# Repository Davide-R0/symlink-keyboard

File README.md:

# Keyboard

## Tools

- Build123d: for the viewer look [external editors](https://build123d.readthedocs.io/en/latest/external.html#external), in general we use: `yet-another-cad-viewer` (c'è una estensione per nvim o vscode?)
- SKiDL: to convert form kicad use tool: `netlist_to_skidl` (TODO: setup kicad liberary for this)
- Openscad to build123 migration: [look here](https://build123d.readthedocs.io/en/latest/OpenSCAD.html)
- for the pcb routing still use kicad editor

## General proprieties

- Layout `4x6+5`
- Parte sinistra il master, destro slave
- Si pososno caricare due firmwere diversi:
  - Bluetooth tra le due parti, se collegato il cavo intermedio e collegato il master al pc si caricano entrambe le schede. In entrambi i casi si può o collegare col cavo al pc per avere cablato il master o col bluetooth col master.
  - Cablato tra le due parti, in questo caso bisogna collegare il cavo tra le due parti e poi si può decidere se collegarla al pc tramite bluetooth o cavo con il master.
- led rgb per key e anche sul retro (led sotto tasti e sul retro sono in due lineee dati separati perchè quando va con batteria funzionano solo quelli sul retro, quando colelgato via cavo funzionano entrambi)
- schermo oled e potenziometro per lato
- Case "Sandwich Mount"
- Framework: `ZMK`, si possono creare moduli in C, supporta BLE e il nice!nano v2.
- Round trackpad (Circle Touchpad), mini touchpad. Il `TM023023-2024` su `Mouser` (c'è sia con overlay che senza, si può usare un nastro personalizzato se si vuole: ) per il connettore: connettore FPC 12-pin, 0.5mm pitch, bottom contact (52746-1271 ?). Altrimenti già completo (ma grande): [splitkb](https://splitkb.com/products/halcyon-cirque-touchpad-module?_pos=1&_sid=2299becd1&_ss=r). NOTA: forse ci sta anche al verisone da 35mm di diametro)

## Components

- Un micorcontroller `nice!nano v2` per lato (Pro Micro NRF52840) (Amazon o Aliexpress)
- Una batteria per lato sotto il microcontroller: `303040`, per la batteria forse fare un dopio fondo (cioè tagliare la back pcb e metterne un'altra che sporge di più sul retro così da poter mettere batterie più spesse (503040 o 503050)) (Aliexpress)
NOTE: le batterie anderebbero sempre circa 400-500mA (`403040`) a destra e 700-800mA (`403050`) a sinistra per consumo giusto.
- Un pannello oled per lato `0.91 inch OLED LCD Display IIC 128×32` (Amazon o Aliexpress)
- Un potenziometro a sinistra: `EC11` con click (LCSC)
- Un Circle Touchpad a destra: [splitkb](https://splitkb.com/products/halcyon-cirque-touchpad-module?_pos=1&_sid=2299becd1&_ss=r). Per la connesisone c'è bisogno di:
  - FPC a 12 pin: `FPC-05F-6PH20` (LCSC) (NOTE: è difficile da saldare? se dovesse essere cercare i "FPC to DIP breakout 12 pin 0.5mm")
  - Per il trackpad c'è un problema: macano i pin, bisogna usare un io expander: `PCA9536D` (4 pin extra) (LCSC)
- I switch `Kailh Choc V2 'Deep Sea' Brown` (tattili, low profile, silenziosi, con alloggio a croce) (Aliexpress)
- Socket per i switch `Kailh Choc Low Profile Socket` compatibili con choc. (Aliexpress) TODO: rivedere socket compatibili!
- Led rgb `SK6812MINI-E` per switch (trought hole) (LCSC)
- Led RGB `SK6812-5050` per la retorilluminazione (x6 per lato) (LCSC)a
- Per i led rgb di va un circuito che scollega l'alimentazione se non servonoe:
  - -- Transistor P-CH mosfet: `AO3401A` SOT-23 (LCSC)
  - -- Transistor N-CH mosfet: `AO3400A` SOT-23 (LCSC)
  - -- Resistena 100kohm: `ERJ6ENF1003V` 0805, per il pull-down per il P-CH (LCSC)
  - -- Resistena 10kohm: `TE05H1002BT` 0805, per il pull-up per il N-CH (LCSC)
  - Al posto dei mosfet grandi e resistenze meglio come: `TPS22917` + condensatore da 1nF: `CL21C102JBCNNNC` (LCSC)
- Resistenze 4.7kohm: `ERJU6RD4701V` 0805, per pullup per SDA e SCL (LCSC)
- Resistenza 400ohm: `TR0805B400RP0525Z` 0805, per l'ingresso DIN dei led (potrebbero esserci sovralimentazioni) (LCSC)
- Diodi: `1N4148W-E3-08` in SOD-123 per i led (cambiare il formato per facilità di saldatura?) (LCSC)
- Connection between split:
  - usb-c ports x2: `TYPE-C 16PIN 2MD`, per connessione tra due parti (LCSC)
  - ESD protection (Chip TVS): `USBLC6-2SC6`
  - PTC fuse (6V 1.5-2A): `1206L150/6V` (NOTE: forse meglio da 2A `1206L200/6V`) (LCSC)
  - Filtro RC per lo shield del usb-c: resistenza: (1kOhm) `RC0805FR-071KL`, condensatore (100nF 100V X7R) `CC0805X7R100V104MN`
  - Resistenza (5.1kohm): `0805W8F5101T5E`, per le connessioni pull-down CC1 CC2 (per alimentaizone)
  - Resistenza (22kohm) con supporto da 1.5A: `ERJ6ENF2202V`, per le connessioni pull-up CC1 CC2 (per alimentaizone)
  - Ideal Diode IC: `MAX40200AUK+T`, per il ritorno di corrente dalla porta (LCSC)
  - --Load switch IO (per protezione da correnti inverse): `TPS22918`
  - -- Diodi Zener da 3.3V: `BZT52C3V3-E3-18`, per protezione da collegamento scorretto (SOD-123) (LCSC)
  - -- resistenze: `0805W8F1000T5E`, 100 ohm 0805 per protezione da collegamento scorretto (LCSC)
- headers low profile: `Mill-Max Mfg. Corp. 315-43-112-41-003000`, to connect the nice!nano to the main pcb (and also the oled display) (LCSC) (OLD: header female connectors: `PM2.54-1X8PM-H85` (o altre versioni...))
- brass spacers M2 (+ viti): `Kit distanziatore in ottone` (Aliexpress)
- slider switch SMD : `PCM12SMTR`, per accendere/spegnere la batteria per ogni lato (LCSC)
- button SMD: verticale: `TL3342F450QG` oppure laterale: `SKSCLDE010`, per mettere la scheda in modalità bootloader. (LCSC)
- PCBs: "Sandwich Mount":
  - Layout:
    - Top Plate: dove voengono incastrati i switch
    - Main PCB: dove c'è tuta la elettornica
    - Bottom Plate: per proteggere la eletronica deall'esterno.
  - Il tutto connesso isnieme con viti M.2 e distanziali in ottone:
    - Tra il main pcb e il Top plate non is mettono distanziali perchè sono gli switch a tenere il palte.
    - Tra main pcb e botton plate: distanziali tra `6-8mm`.
  - Per la pendenza o si mettono distanziali assimmetrici,oppure si usa il `Tenting Puck`, (JLCPCB)
- Livellatore di tensione (Level Shifter): `SN74LVC1T45DBVR` per la linea dati dei led (LCSC)
- Per prioteggere sovratensioni TX/RX un Logic Buffer: `SN74LVC2G34DBVR` (LCSC)
- --Diodo Schottky: `SS14`, per il ritorno della batteria quando sono collegati tramite filo le due parti (LCSC)
- Kampton tape: per l'isolamento e resistenza al calore (Aliexpress)
- Pasta saldante: per componenti smd (Aliexpress)

Switch Kailh Choc V2: Ottimi, ma ricorda che hanno un'altezza diversa dai V1. Il tuo "Top Plate" deve avere uno spessore di $1.2\text{ mm}$ o $1.5\text{ mm}$ (taglio laser o PCB) per permettere agli switch di "cliccare" correttamente in posizione.

NOTE: per i componenti smd i formati da scegliere sono:

- SOT-23 per i chip a più gambe
- 0805 per R, C e componenti a 2 gambe

QT_QPA_PLATFORM=xcb freecad

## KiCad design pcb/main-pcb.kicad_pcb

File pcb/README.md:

skidl in python

 NOTE: per nvim è meglio lsp: basedpyright perchè più robusto

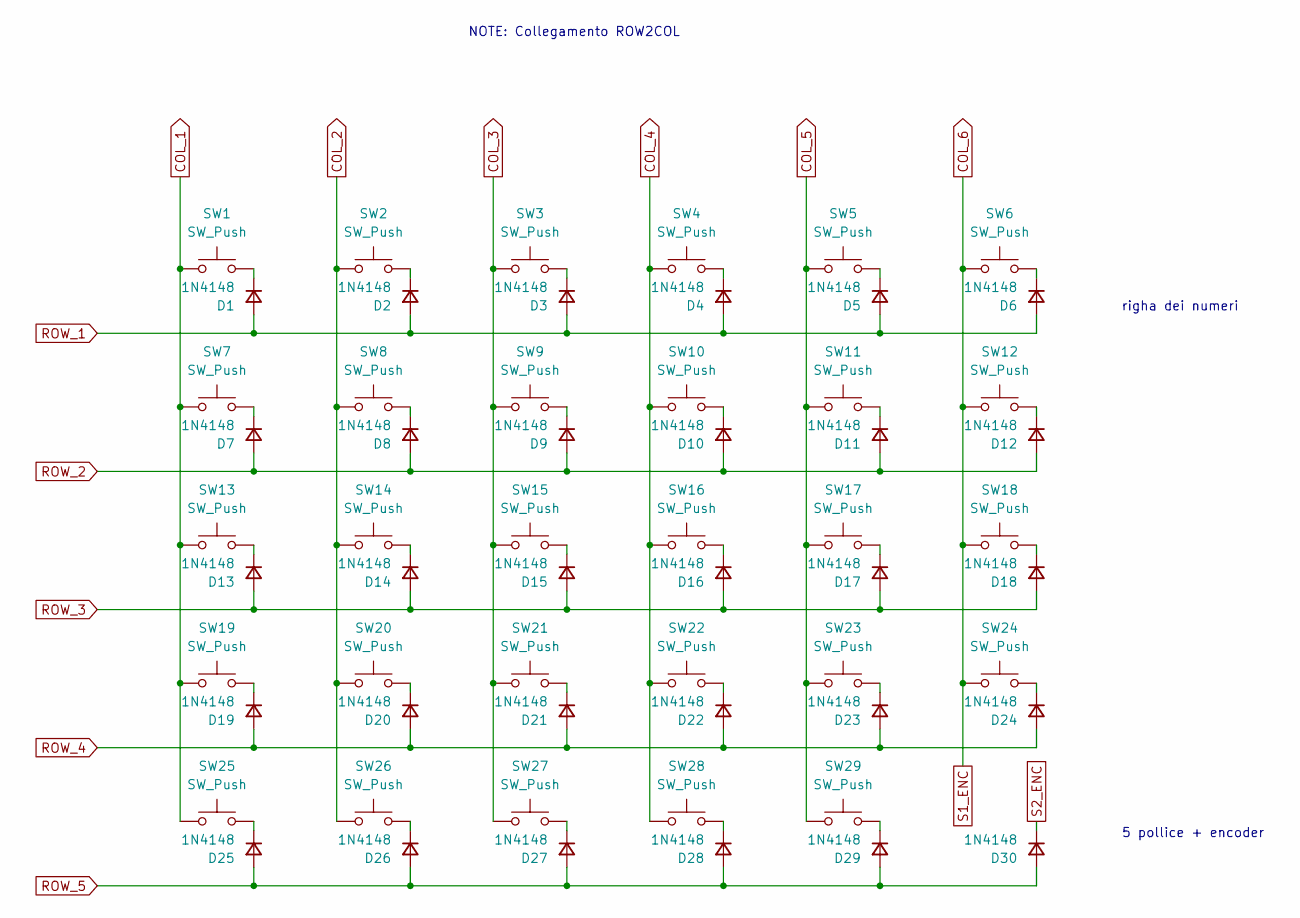
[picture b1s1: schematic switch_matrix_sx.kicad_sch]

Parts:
D1, D2, D3, D4, D5, D6, D7, D8, D9, D10, D11, D12, D13, D14, D15, D16, D17, D18, D19, D20, D21, D22, D23, D24, D25, D26, D27, D28, D29, D30: 1N4148; D_SOD-123
SW1, SW2, SW3, SW4, SW5, SW6, SW7, SW8, SW9, SW10, SW11, SW12, SW13, SW14, SW15, SW16, SW17, SW18, SW19, SW20, SW21, SW22, SW23, SW24, SW25, SW26, SW27, SW28, SW29: SW_Push; SW_Hotswap_Kailh_Choc_V2_1.00u

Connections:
COL_1: SW1.1, SW7.1, SW13.1, SW19.1, SW25.1; also elsewhere on the board
COL_2: SW2.1, SW8.1, SW14.1, SW20.1, SW26.1; also elsewhere on the board
COL_3: SW3.1, SW9.1, SW15.1, SW21.1, SW27.1; also elsewhere on the board
COL_4: SW4.1, SW10.1, SW16.1, SW22.1, SW28.1; also elsewhere on the board
COL_5: SW5.1, SW11.1, SW17.1, SW23.1, SW29.1; also elsewhere on the board
COL_6: SW6.1, SW12.1, SW18.1, SW24.1; also elsewhere on the board
unnamed: D1.1 (K), SW1.2
unnamed: D2.1 (K), SW2.2
unnamed: D3.1 (K), SW3.2
unnamed: D4.1 (K), SW4.2
unnamed: D5.1 (K), SW5.2
unnamed: D6.1 (K), SW6.2
unnamed: D7.1 (K), SW7.2
unnamed: D8.1 (K), SW8.2
unnamed: D9.1 (K), SW9.2
unnamed: D10.1 (K), SW10.2
unnamed: D11.1 (K), SW11.2
unnamed: D12.1 (K), SW12.2
unnamed: D13.1 (K), SW13.2
unnamed: D14.1 (K), SW14.2
unnamed: D15.1 (K), SW15.2
unnamed: D16.1 (K), SW16.2
unnamed: D17.1 (K), SW17.2
unnamed: D18.1 (K), SW18.2
unnamed: D19.1 (K), SW19.2
unnamed: D20.1 (K), SW20.2
unnamed: D21.1 (K), SW21.2
unnamed: D22.1 (K), SW22.2
unnamed: D23.1 (K), SW23.2
unnamed: D24.1 (K), SW24.2
unnamed: D25.1 (K), SW25.2
unnamed: D26.1 (K), SW26.2
unnamed: D27.1 (K), SW27.2
unnamed: D28.1 (K), SW28.2
unnamed: D29.1 (K), SW29.2
ROW_1: D1.2 (A), D2.2 (A), D3.2 (A), D4.2 (A), D5.2 (A), D6.2 (A); also elsewhere on the board
ROW_2: D7.2 (A), D8.2 (A), D9.2 (A), D10.2 (A), D11.2 (A), D12.2 (A); also elsewhere on the board
ROW_3: D13.2 (A), D14.2 (A), D15.2 (A), D16.2 (A), D17.2 (A), D18.2 (A); also elsewhere on the board
ROW_4: D19.2 (A), D20.2 (A), D21.2 (A), D22.2 (A), D23.2 (A), D24.2 (A); also elsewhere on the board
ROW_5: D25.2 (A), D26.2 (A), D27.2 (A), D28.2 (A), D29.2 (A), D30.2 (A); also elsewhere on the board
S2_ENC: D30.1 (K); also elsewhere on the board

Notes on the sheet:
NOTE: Collegamento ROW2COL
5 pollice + encoder
righa dei numeri

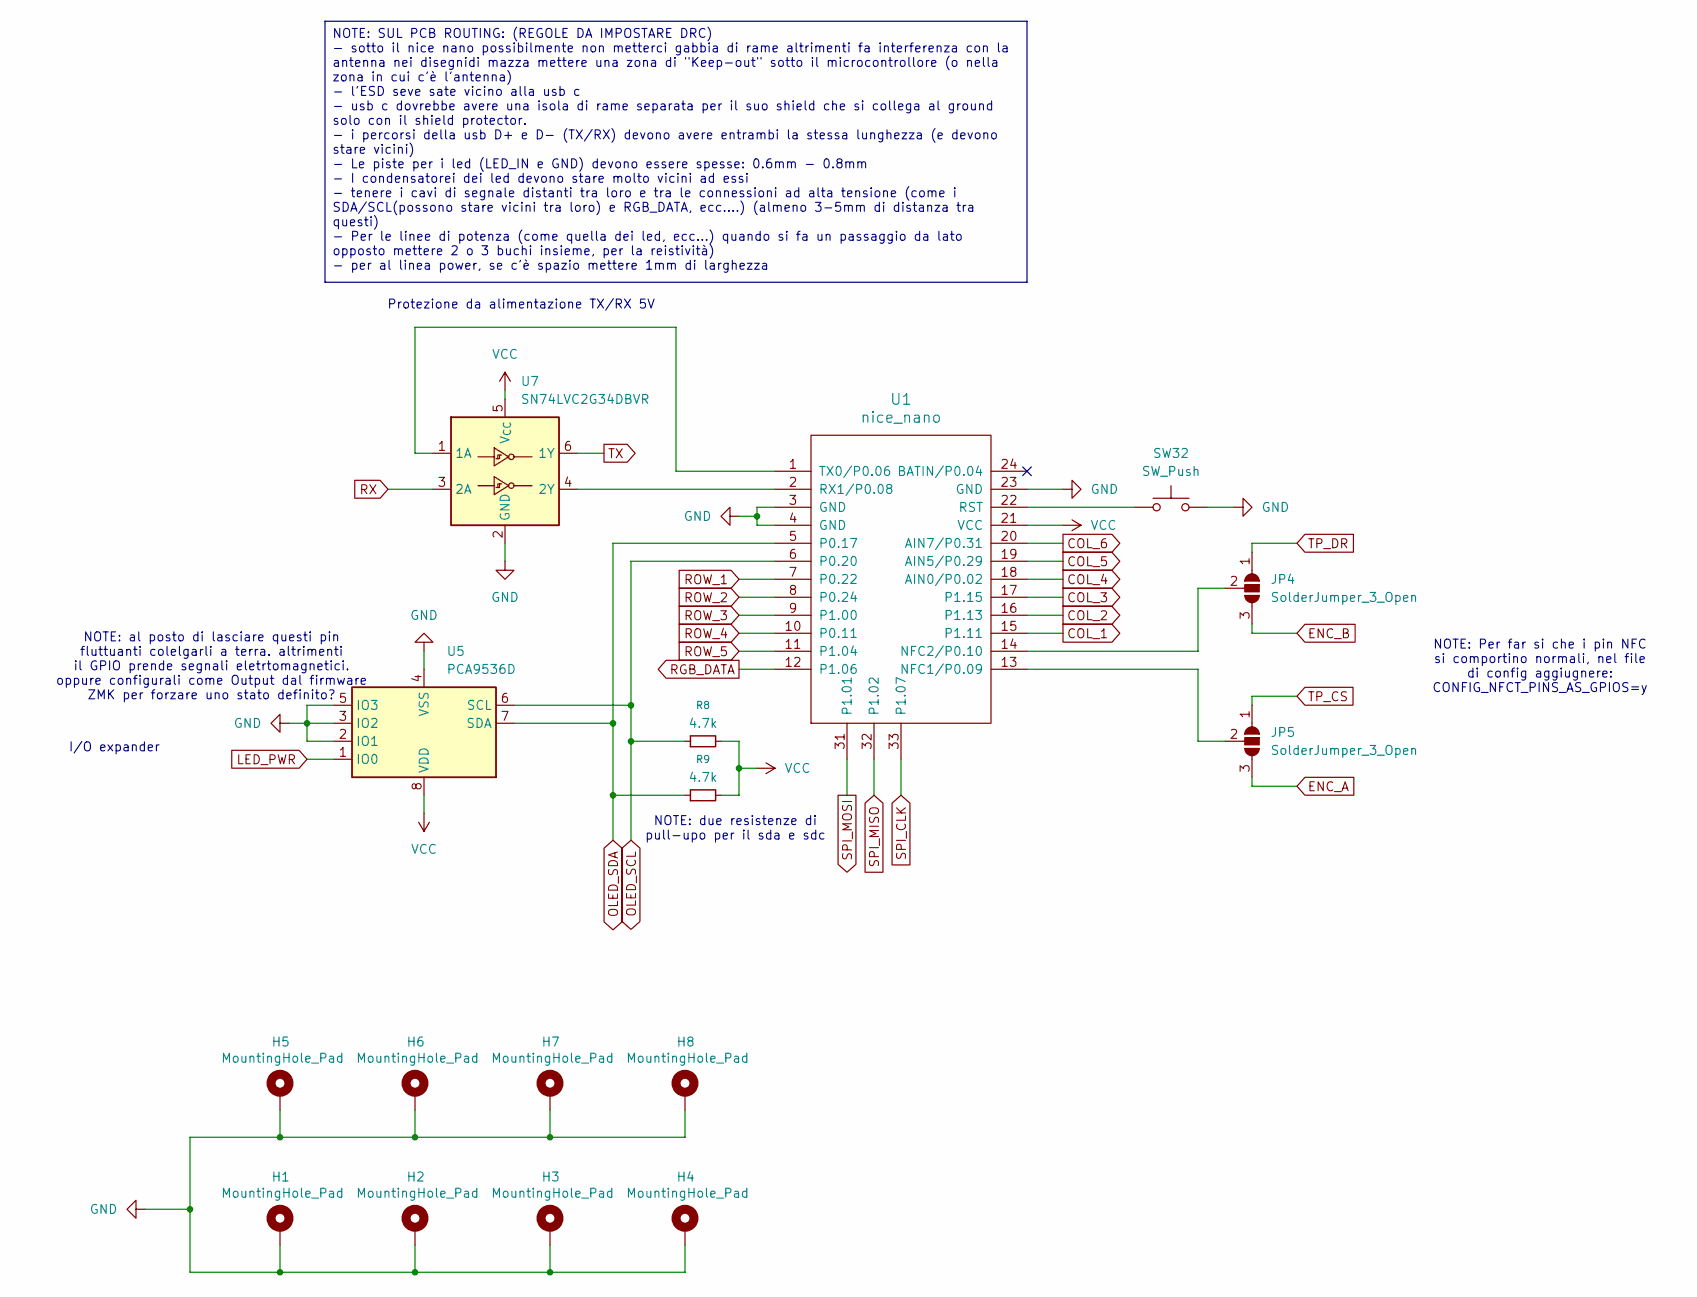
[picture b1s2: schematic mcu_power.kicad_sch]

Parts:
H1, H2, H3, H4, H5, H6, H7, H8: MountingHole_Pad
JP4, JP5: SolderJumper_3_Open; SolderJumper-3_P1.3mm_Open_RoundedPad1.0x1.5mm_NumberLabels
R8, R9: 4.7k; R_0805_2012Metric_Pad1.20x1.40mm_HandSolder
SW32: SW_Push; SW_SPST_TL3342
U1: nice_nano
U5: PCA9536D; SOIC-8_3.9x4.9mm_P1.27mm
U7: SN74LVC2G34DBVR; SOT-23-6

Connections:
COL_1: U1.15 (P1.11); also elsewhere on the board
COL_2: U1.16 (P1.13); also elsewhere on the board
COL_3: U1.17 (P1.15); also elsewhere on the board
COL_4: U1.18 (AIN0/P0.02); also elsewhere on the board
COL_5: U1.19 (AIN5/P0.29); also elsewhere on the board
COL_6: U1.20 (AIN7/P0.31); also elsewhere on the board
ENC_A: JP5.3 (B); also elsewhere on the board
ENC_B: JP4.3 (B); also elsewhere on the board
GND: H1.1, H2.1, H3.1, H4.1, H5.1, H6.1, H7.1, H8.1, SW32.2, U1.3 (GND), U1.4 (GND), U1.23 (GND), U5.2 (IO1), U5.3 (IO2), U5.4 (VSS), U5.5 (IO3), U7.2 (GND); also elsewhere on the board
LED_PWR: U5.1 (IO0); also elsewhere on the board
unnamed: JP4.2 (C), U1.14 (NFC2/P0.10)
unnamed: JP5.2 (C), U1.13 (NFC1/P0.09)
unnamed: SW32.1, U1.22 (RST)
unnamed: U1.2 (RX1/P0.08), U7.4 (2Y)
unnamed: U1.1 (TX0/P0.06), U7.1 (1A)
OLED_SCL: R8.1, U1.6 (P0.20), U5.6 (SCL); also elsewhere on the board
OLED_SDA: R9.1, U1.5 (P0.17), U5.7 (SDA); also elsewhere on the board
RGB_DATA: U1.12 (P1.06); also elsewhere on the board
ROW_1: U1.7 (P0.22); also elsewhere on the board
ROW_2: U1.8 (P0.24); also elsewhere on the board
ROW_3: U1.9 (P1.00); also elsewhere on the board
ROW_4: U1.10 (P0.11); also elsewhere on the board
ROW_5: U1.11 (P1.04); also elsewhere on the board
RX: U7.3 (2A); also elsewhere on the board
SPI_CLK: U1.33 (P1.07); also elsewhere on the board
SPI_MISO: U1.32 (P1.02); also elsewhere on the board
SPI_MOSI: U1.31 (P1.01); also elsewhere on the board
TP_CS: JP5.1 (A); also elsewhere on the board
TP_DR: JP4.1 (A); also elsewhere on the board
TX: U7.6 (1Y); also elsewhere on the board
VCC: R8.2, R9.2, U1.21 (VCC), U5.8 (VDD), U7.5 (V_{CC}); also elsewhere on the board

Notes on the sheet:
NOTE: Per far si che i pin NFC si comportino normali, nel file di config aggiugnere: CONFIG_NFCT_PINS_AS_GPIOS=y
NOTE: al posto di lasciare questi pin fluttuanti colelgarli a terra. altrimenti il GPIO prende segnali eletrtomagnetici. oppure configurali come Output dal firmware ZMK per forzare uno stato definito?
I/O expander
Protezione da alimentazione TX/RX 5V
NOTE: due resistenze di pull-upo per il sda e sdc
NOTE: SUL PCB ROUTING: (REGOLE DA IMPOSTARE DRC) - sotto il nice nano possibilmente non metterci gabbia di rame altrimenti fa interferenza con la antenna nei disegnidi mazza mettere una zona di "Keep-out" sotto il microcontrollore (o nella zona in cui c'è l'antenna) - l'ESD seve sate vicino alla us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

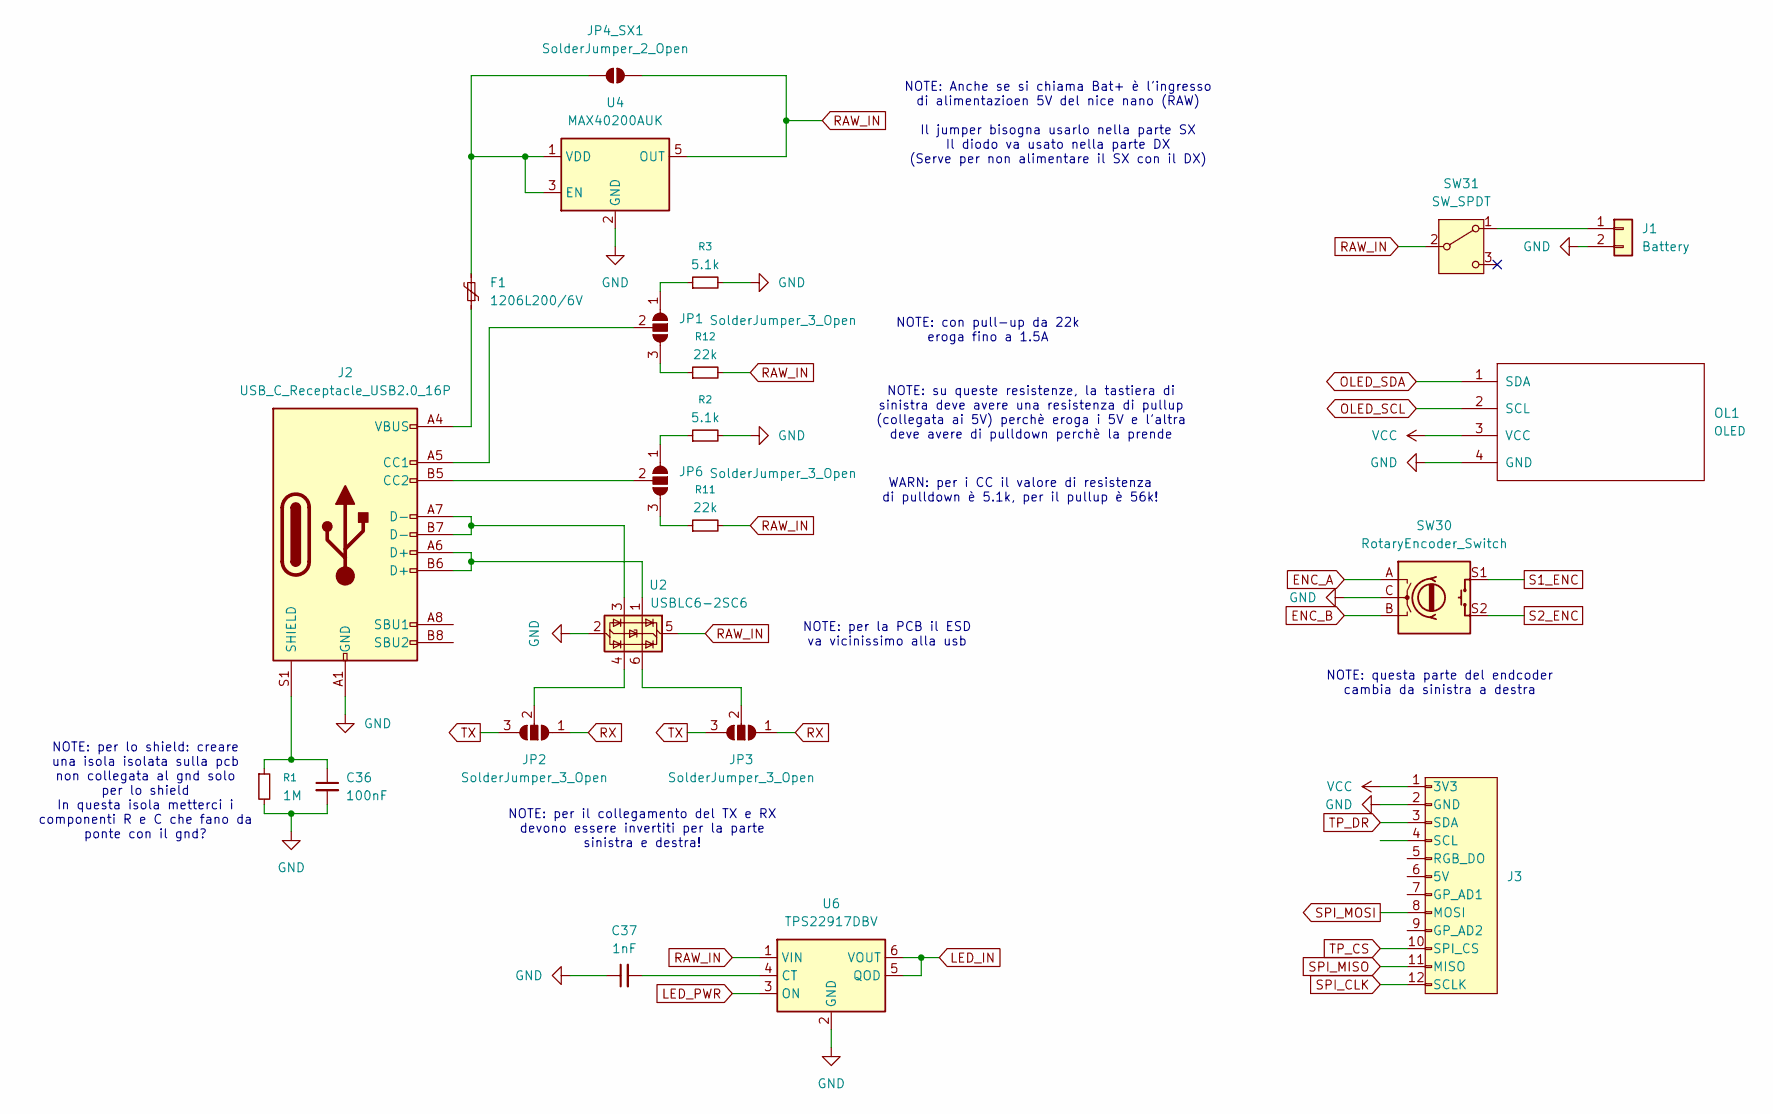
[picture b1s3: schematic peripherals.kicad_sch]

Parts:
C36: 100nF; C_0805_2012Metric_Pad1.18x1.45mm_HandSolder
C37: 1nF; C_0805_2012Metric_Pad1.18x1.45mm_HandSolder
F1: 1206L200/6V; Fuse_1206_3216Metric
J1: Battery; JST_PH_S2B-PH-K_1x02_P2.00mm_Horizontal
J2: USB_C_Receptacle_USB2.0_16P; USB_C_Receptacle_HRO_TYPE-C-31-M-12
J3: JUSHUO_AFA07-S12FCA-00_1x12-1MP_P1.0mm_Horizontal
JP1, JP2, JP3, JP6: SolderJumper_3_Open; SolderJumper-3_P1.3mm_Open_RoundedPad1.0x1.5mm_NumberLabels
JP4_SX1: SolderJumper_2_Open; SolderJumper-2_P1.3mm_Open_RoundedPad1.0x1.5mm
OL1: OLED; OLED_v2
R1: 1M; R_0805_2012Metric_Pad1.20x1.40mm_HandSolder
R2, R3: 5.1k; R_0805_2012Metric_Pad1.20x1.40mm_HandSolder
R11, R12: 22k; R_0805_2012Metric_Pad1.20x1.40mm_HandSolder
SW30: RotaryEncoder_Switch; RotaryEncoder_Alps_EC11E-Switch_Vertical_H20mm
SW31: SW_SPDT; SW_SPDT_PCM12
U2: USBLC6-2SC6; SOT-23-6
U4: MAX40200AUK; SOT-23-5
U6: TPS22917DBV; SOT-23-6

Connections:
COL_6: SW30.S1; also elsewhere on the board
ENC_A: SW30.A; also elsewhere on the board
ENC_B: SW30.B; also elsewhere on the board
GND: C36.2, C37.1, J1.2, J2.A1 (GND), J2.A12 (GND), J2.B1 (GND), J2.B12 (GND), J3.2 (GND), OL1.4 (GND), R1.2, R2.2, R3.2, SW30.C, U2.2 (GND), U4.2 (GND), U6.2 (GND); also elsewhere on the board
LED_IN: U6.5 (QOD), U6.6 (VOUT); also elsewhere on the board
LED_PWR: U6.3 (ON); also elsewhere on the board
unnamed: F1.1, J2.A4 (VBUS), J2.A9 (VBUS), J2.B4 (VBUS), J2.B9 (VBUS)
unnamed: J1.1, SW31.1 (A)
unnamed: J2.A5 (CC1), JP1.2 (C)
unnamed: J2.B5 (CC2), JP6.2 (C)
unnamed: J2.A6 (D+), J2.B6 (D+), U2.1 (I/O1)
unnamed: J2.A7 (D-), J2.B7 (D-), U2.3 (I/O2)
unnamed: C36.1, J2.S1 (SHIELD), R1.1
unnamed: JP1.1 (A), R3.1
unnamed: JP1.3 (B), R12.1
unnamed: JP2.2 (C), U2.4 (I/O2)
unnamed: JP3.2 (C), U2.6 (I/O1)
unnamed: F1.2, JP4_SX1.2 (B), U4.1 (VDD), U4.3 (EN)
unnamed: JP6.1 (A), R2.1
unnamed: JP6.3 (B), R11.1
unnamed: C37.2, U6.4 (CT)
OLED_SCL: OL1.2 (SCL); also elsewhere on the board
OLED_SDA: OL1.1 (SDA); also elsewhere on the board
RAW_IN: JP4_SX1.1 (A), R11.2, R12.2, SW31.2 (B), U2.5 (VBUS), U4.5 (OUT), U6.1 (VIN); also elsewhere on the board
RX: JP2.1 (A), JP3.1 (A); also elsewhere on the board
S2_ENC: SW30.S2; also elsewhere on the board
SPI_CLK: J3.12 (SCLK); also elsewhere on the board
SPI_MISO: J3.11 (MISO); also elsewhere on the board
SPI_MOSI: J3.8 (MOSI); also elsewhere on the board
TP_CS: J3.10 (SPI_CS); also elsewhere on the board
TP_DR: J3.3 (SDA); also elsewhere on the board
TX: JP2.3 (B), JP3.3 (B); also elsewhere on the board
VCC: J3.1 (3V3), OL1.3 (VCC); also elsewhere on the board

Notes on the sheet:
NOTE: per lo shield: creare una isola isolata sulla pcb non collegata al gnd solo per lo shield In questa isola metterci i componenti R e C che fano da ponte con il gnd?
NOTE: questa parte del endcoder cambia da sinistra a destra
WARN: per i CC il valore di resistenza di pulldown è 5.1k, per il pullup è 56k!
NOTE: per il collegamento del TX e RX devono essere invertiti per la parte sinistra e destra!
NOTE: per la PCB il ESD va vicinissimo alla usb
NOTE: su queste resistenze, la tastiera di sinistra deve avere una resistenza di pullup (collegata ai 5V) perchè eroga i 5V e l'altra deve avere di pulldown perchè la prende
NOTE: Anche se si chiama Bat+ è l'ingresso di alimentazioen 5V del nice nano (RAW) Il jumper bisogna usarlo nella parte SX Il diodo va usato nella parte DX (Serve per non alimentare il SX con il DX)
NOTE: con pull-up da 22k eroga fino a 1.5A

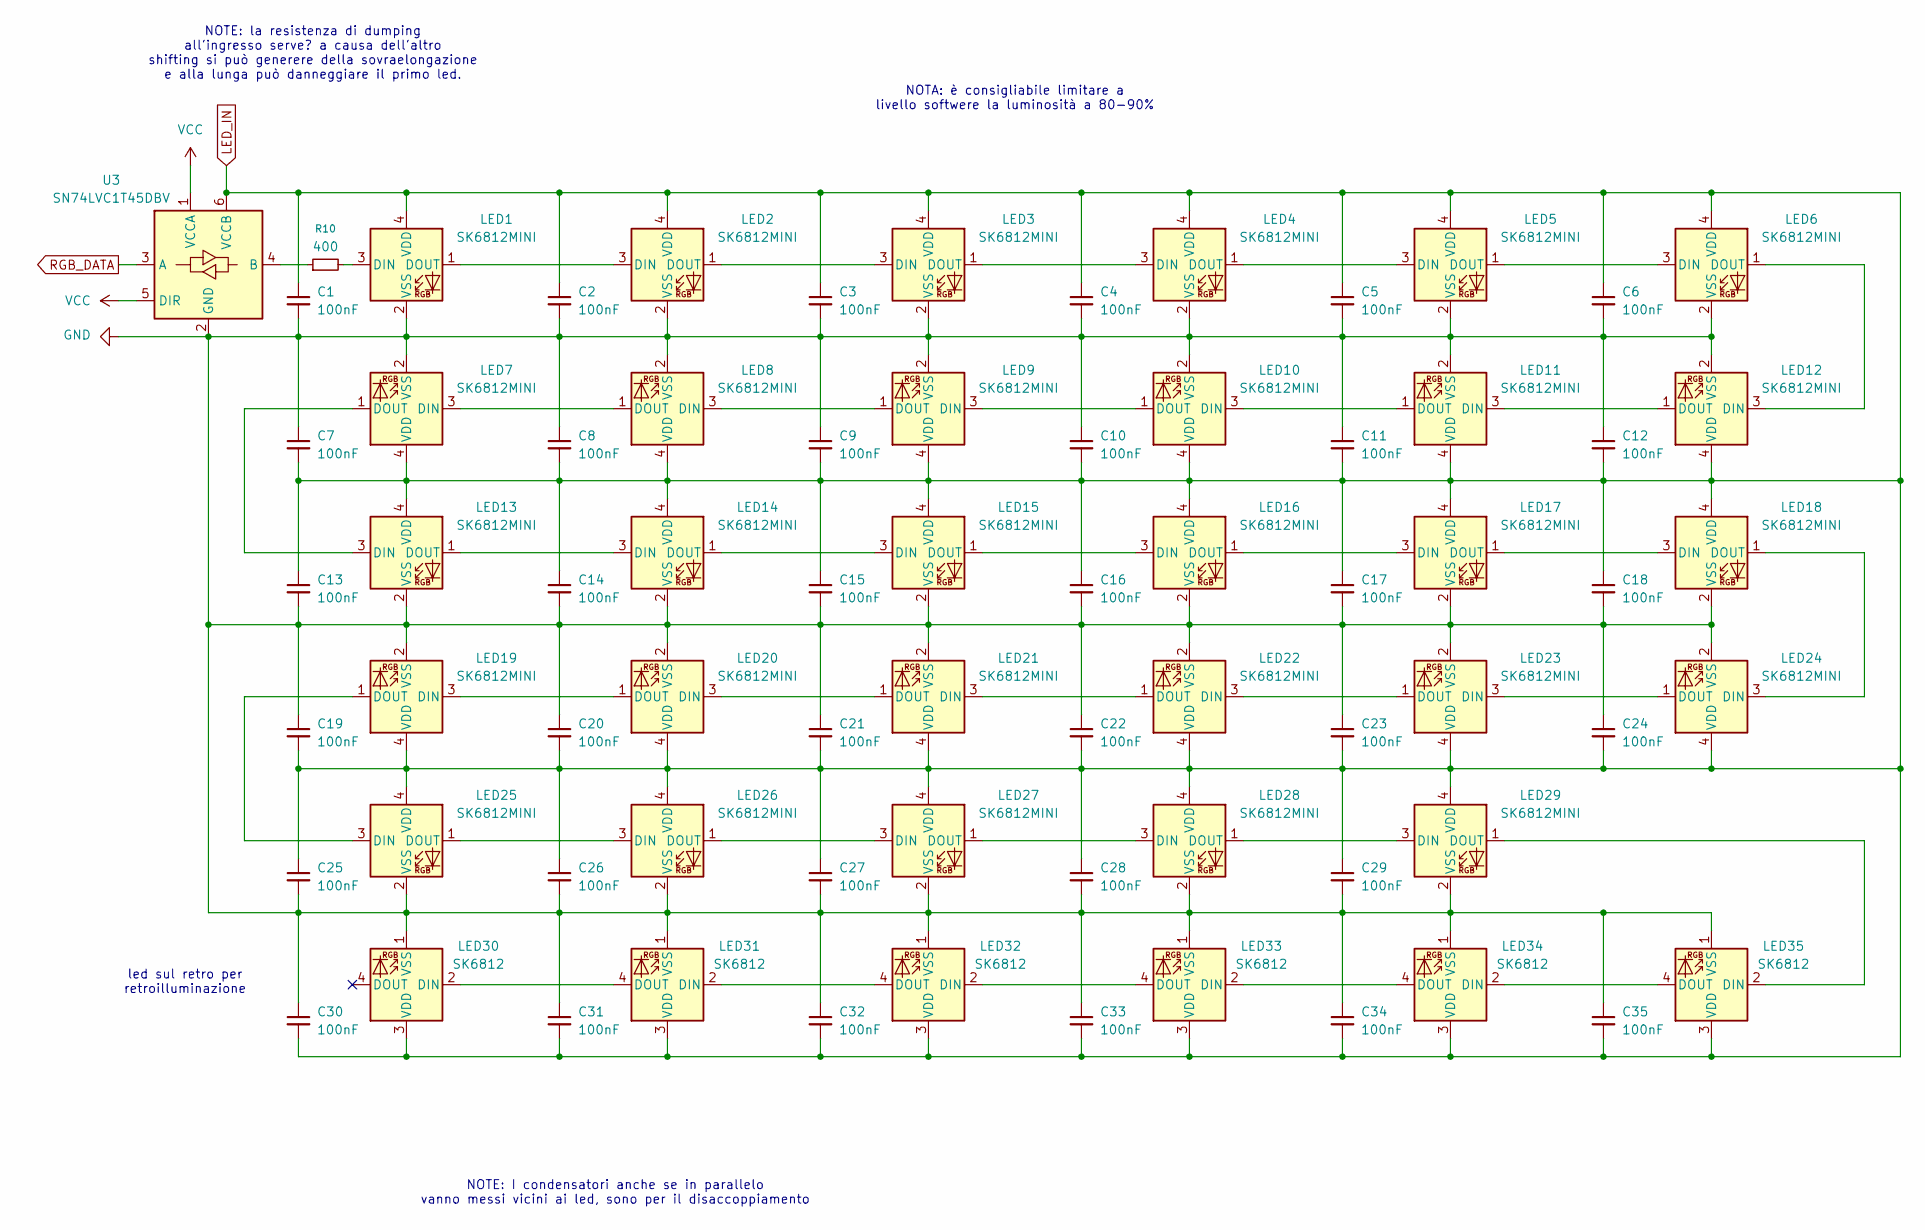
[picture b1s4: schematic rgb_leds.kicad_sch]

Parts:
C1, C2, C3, C4, C5, C6, C7, C8, C9, C10, C11, C12, C13, C14, C15, C16, C17, C18, C19, C20, C21, C22, C23, C24, C25, C26, C27, C28, C29, C30, C31, C32, C33, C34, C35: 100nF; C_0805_2012Metric
LED1, LED2, LED3, LED4, LED5, LED6, LED7, LED8, LED9, LED10, LED11, LED12, LED13, LED14, LED15, LED16, LED17, LED18, LED19, LED20, LED21, LED22, LED23, LED24, LED25, LED26, LED27, LED28, LED29: SK6812MINI; SK6812-MINI-E
LED30, LED31, LED32, LED33, LED34, LED35: SK6812; LED_OPSCO_SK6812_PLCC4_5.0x5.0mm_P3.1mm
R10: 400; R_0805_2012Metric_Pad1.20x1.40mm_HandSolder
U3: SN74LVC1T45DBV; SOT-23-6

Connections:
GND: C1.2, C2.2, C3.2, C4.2, C5.2, C6.2, C7.1, C8.1, C9.1, C10.1, C11.1, C12.1, C13.2, C14.2, C15.2, C16.2, C17.2, C18.2, C19.1, C20.1, C21.1, C22.1, C23.1, C24.1, C25.2, C26.2, C27.2, C28.2, C29.2, C30.1, C31.1, C32.1, C33.1, C34.1, C35.1, LED1.2 (VSS), LED2.2 (VSS), LED3.2 (VSS), LED4.2 (VSS), LED5.2 (VSS), LED6.2 (VSS), LED7.2 (VSS), LED8.2 (VSS), LED9.2 (VSS), LED10.2 (VSS), LED11.2 (VSS), LED12.2 (VSS), LED13.2 (VSS), LED14.2 (VSS), LED15.2 (VSS), LED16.2 (VSS), LED17.2 (VSS), LED18.2 (VSS), LED19.2 (VSS), LED20.2 (VSS), LED21.2 (VSS), LED22.2 (VSS), LED23.2 (VSS), LED24.2 (VSS), LED25.2 (VSS), LED26.2 (VSS), LED27.2 (VSS), LED28.2 (VSS), LED29.2 (VSS), LED30.1 (VSS), LED31.1 (VSS), LED32.1 (VSS), LED33.1 (VSS), LED34.1 (VSS), LED35.1 (VSS), U3.2 (GND); also elsewhere on the board
LED_IN: C1.1, C2.1, C3.1, C4.1, C5.1, C6.1, C7.2, C8.2, C9.2, C10.2, C11.2, C12.2, C13.1, C14.1, C15.1, C16.1, C17.1, C18.1, C19.2, C20.2, C21.2, C22.2, C23.2, C24.2, C25.1, C26.1, C27.1, C28.1, C29.1, C30.2, C31.2, C32.2, C33.2, C34.2, C35.2, LED1.4 (VDD), LED2.4 (VDD), LED3.4 (VDD), LED4.4 (VDD), LED5.4 (VDD), LED6.4 (VDD), LED7.4 (VDD), LED8.4 (VDD), LED9.4 (VDD), LED10.4 (VDD), LED11.4 (VDD), LED12.4 (VDD), LED13.4 (VDD), LED14.4 (VDD), LED15.4 (VDD), LED16.4 (VDD), LED17.4 (VDD), LED18.4 (VDD), LED19.4 (VDD), LED20.4 (VDD), LED21.4 (VDD), LED22.4 (VDD), LED23.4 (VDD), LED24.4 (VDD), LED25.4 (VDD), LED26.4 (VDD), LED27.4 (VDD), LED28.4 (VDD), LED29.4 (VDD), LED30.3 (VDD), LED31.3 (VDD), LED32.3 (VDD), LED33.3 (VDD), LED34.3 (VDD), LED35.3 (VDD), U3.6 (VCCB); also elsewhere on the board
unnamed: LED1.3 (DIN), R10.2
unnamed: LED1.1 (DOUT), LED2.3 (DIN)
unnamed: LED2.1 (DOUT), LED3.3 (DIN)
unnamed: LED3.1 (DOUT), LED4.3 (DIN)
unnamed: LED4.1 (DOUT), LED5.3 (DIN)
unnamed: LED5.1 (DOUT), LED6.3 (DIN)
unnamed: LED7.3 (DIN), LED8.1 (DOUT)
unnamed: LED8.3 (DIN), LED9.1 (DOUT)
unnamed: LED10.3 (DIN), LED11.1 (DOUT)
unnamed: LED9.3 (DIN), LED10.1 (DOUT)
unnamed: LED11.3 (DIN), LED12.1 (DOUT)
unnamed: LED6.1 (DOUT), LED12.3 (DIN)
unnamed: LED7.1 (DOUT), LED13.3 (DIN)
unnamed: LED13.1 (DOUT), LED14.3 (DIN)
unnamed: LED14.1 (DOUT), LED15.3 (DIN)
unnamed: LED15.1 (DOUT), LED16.3 (DIN)
unnamed: LED16.1 (DOUT), LED17.3 (DIN)
unnamed: LED17.1 (DOUT), LED18.3 (DIN)
unnamed: LED18.1 (DOUT), LED24.3 (DIN)
unnamed: LED19.3 (DIN), LED20.1 (DOUT)
unnamed: LED19.1 (DOUT), LED25.3 (DIN)
unnamed: LED20.3 (DIN), LED21.1 (DOUT)
unnamed: LED21.3 (DIN), LED22.1 (DOUT)
unnamed: LED22.3 (DIN), LED23.1 (DOUT)
unnamed: LED23.3 (DIN), LED24.1 (DOUT)
unnamed: LED25.1 (DOUT), LED26.3 (DIN)
unnamed: LED26.1 (DOUT), LED27.3 (DIN)
unnamed: LED27.1 (DOUT), LED28.3 (DIN)
unnamed: LED28.1 (DOUT), LED29.3 (DIN)
unnamed: LED29.1 (DOUT), LED35.2 (DIN)
unnamed: LED30.2 (DIN), LED31.4 (DOUT)
unnamed: LED31.2 (DIN), LED32.4 (DOUT)
unnamed: LED32.2 (DIN), LED33.4 (DOUT)
unnamed: LED33.2 (DIN), LED34.4 (DOUT)
unnamed: LED34.2 (DIN), LED35.4 (DOUT)
unnamed: R10.1, U3.4 (B)
RGB_DATA: U3.3 (A); also elsewhere on the board
VCC: U3.1 (VCCA), U3.5 (DIR); also elsewhere on the board

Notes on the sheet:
led sul retro per retroilluminazione
NOTE: I condensatori anche se in parallelo vanno messi vicini ai led, sono per il disaccoppiamento
NOTA: è consigliabile limitare a livello softwere la luminosità a 80-90%
NOTE: la resistenza di dumping all'ingresso serve? a causa dell'altro shifting si può generere della sovraelongazione e alla lunga può danneggiare il primo led.

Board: 2 copper layers, 162 parts (101 on the bottom side), 114 nets, no tracks yet.

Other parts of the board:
D31_DX1: SS14; D_SMA

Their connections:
RAW_IN: D31_DX1.1 (K); also elsewhere on the board

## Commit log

2026-03-07 First commit.
